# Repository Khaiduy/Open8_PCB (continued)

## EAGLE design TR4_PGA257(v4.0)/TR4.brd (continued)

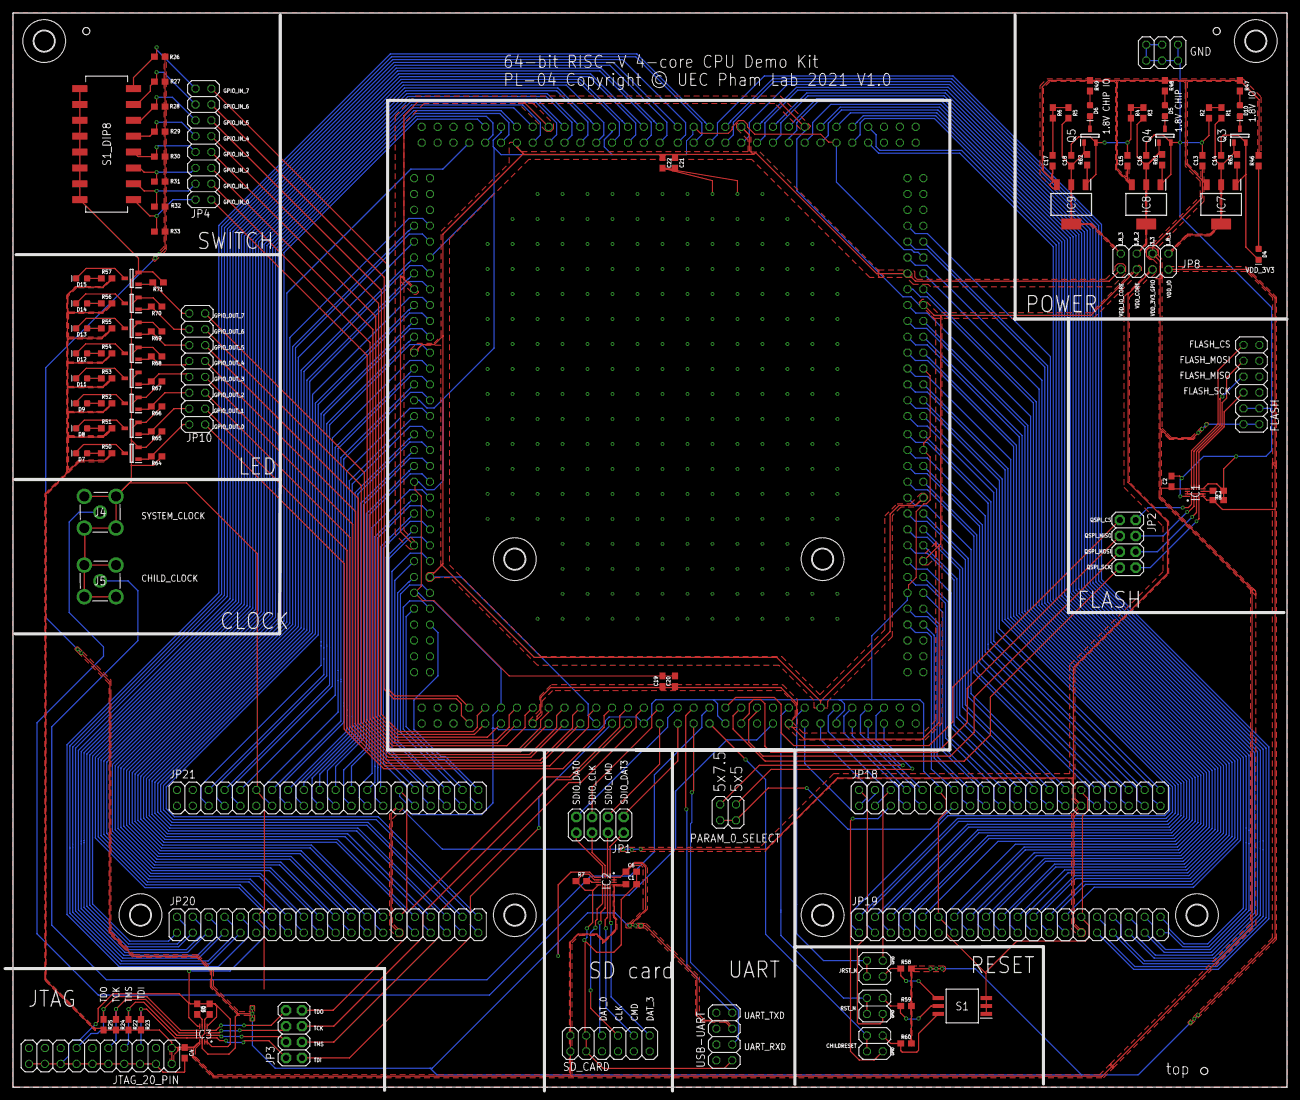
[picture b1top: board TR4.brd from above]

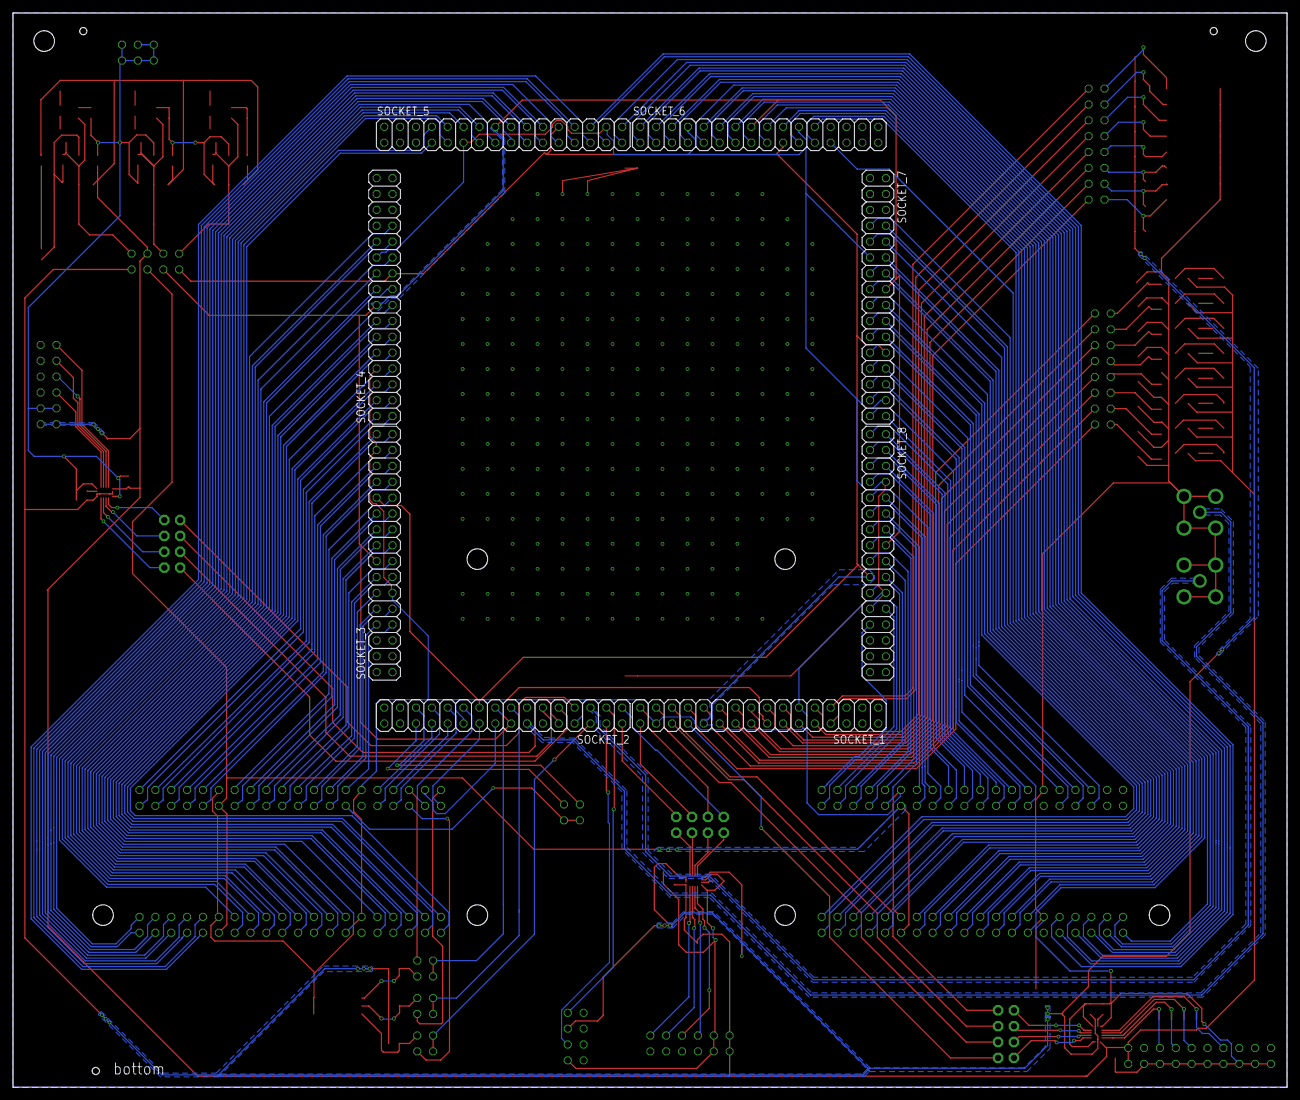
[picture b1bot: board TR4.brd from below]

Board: 2 copper layers, 204.0 x 172.0 mm, 131 parts (8 on the bottom side), 255 nets.

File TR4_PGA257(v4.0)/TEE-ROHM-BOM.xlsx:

Comment | Designator | Footprint | LCSC Part #（optional）
0.1uF | C1, C2, C3, C4, C5, C6, C19, C21 | 603 | C77055
100uF | C14, C16, C18 | 603
10KOHM | R7, R8, R9, R22, R23, R24, R25, R26, R27, R28, R29, R30, R31, R32, R33, R58, R5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 | 603 | C25804
10uF | C13, C15, C17, C20, C22 | 603 | C1691
15KOHM | R1, R3, R5 | 603 | C22809
Switch | S1_DIP8 | 2198LPST | C314503
330OHM | R46, R47, R48, R49, R50, R51, R52, R53, R54, R55, R56, R57 | 603 | C23138
6.8KOHM | R2, R4, R6 | 603 | C23212
BSH103,235 | Q3, Q4, Q5, Q6, Q7, Q8, Q9, Q10, Q11, Q12, Q13 | SOT-23-3 | C88711
DSHP03TSGET | S1 | SW-SMD | C50844
LED0 | D4, D5, D6, D7, D8, D9, D10, D11, D12, D13, D14, D15 | LED-0603 | C2286
LM1117IMPX-ADJ/NOPB | IC7, IC8, IC9 | SOT-223 | C19228
SN74AVC4T774RSVR | IC1, IC2, IC3 | UQFN-16 | C779392

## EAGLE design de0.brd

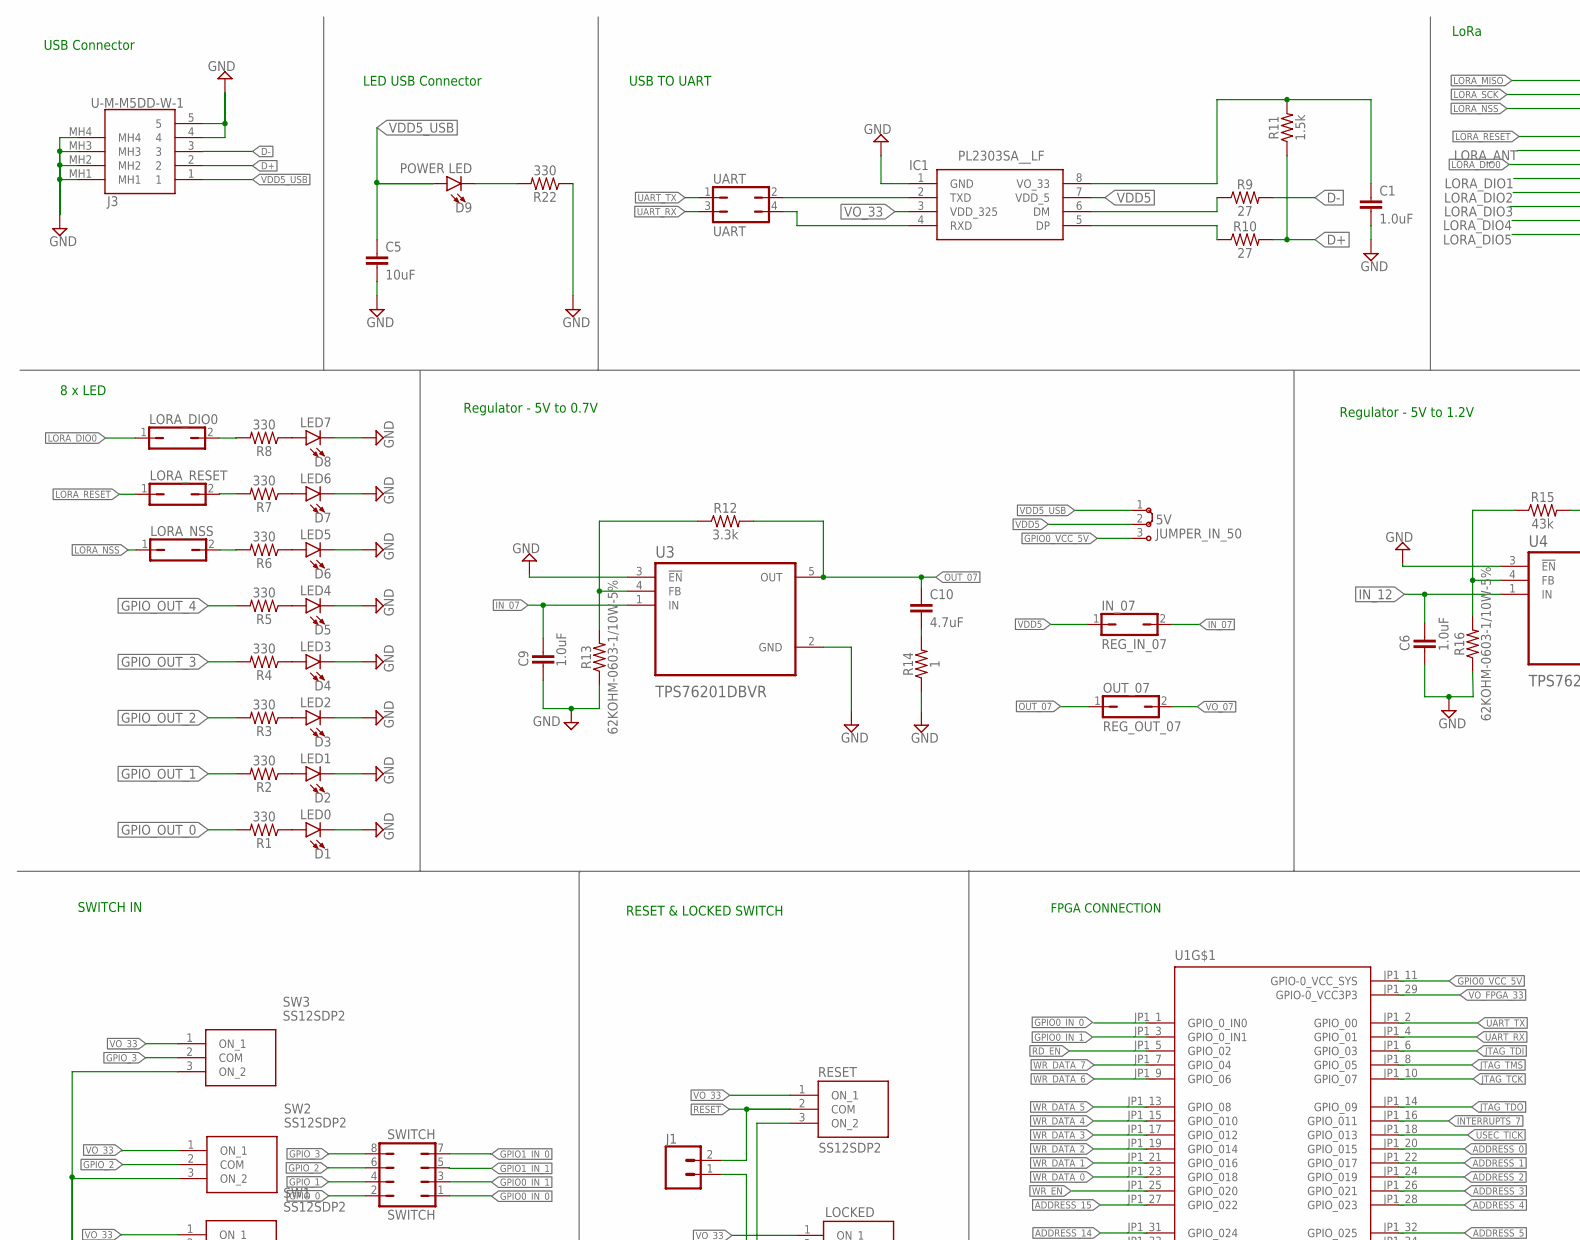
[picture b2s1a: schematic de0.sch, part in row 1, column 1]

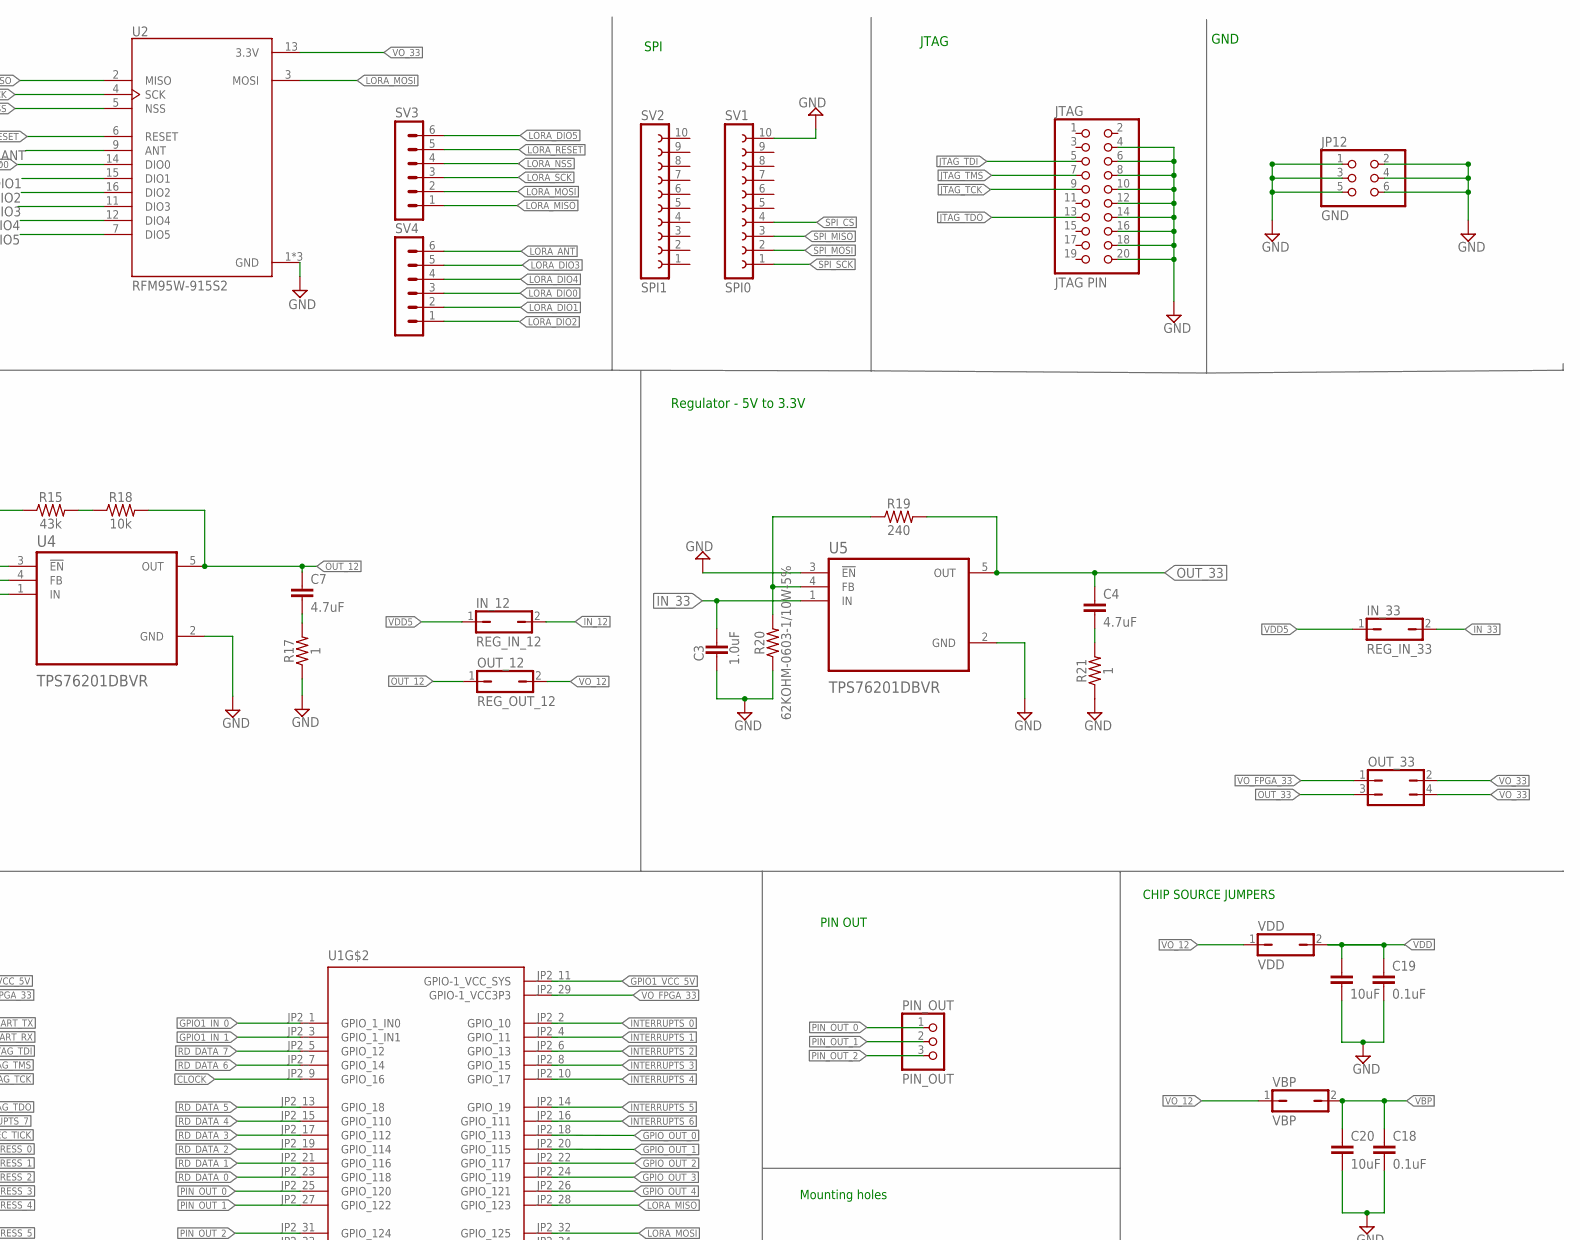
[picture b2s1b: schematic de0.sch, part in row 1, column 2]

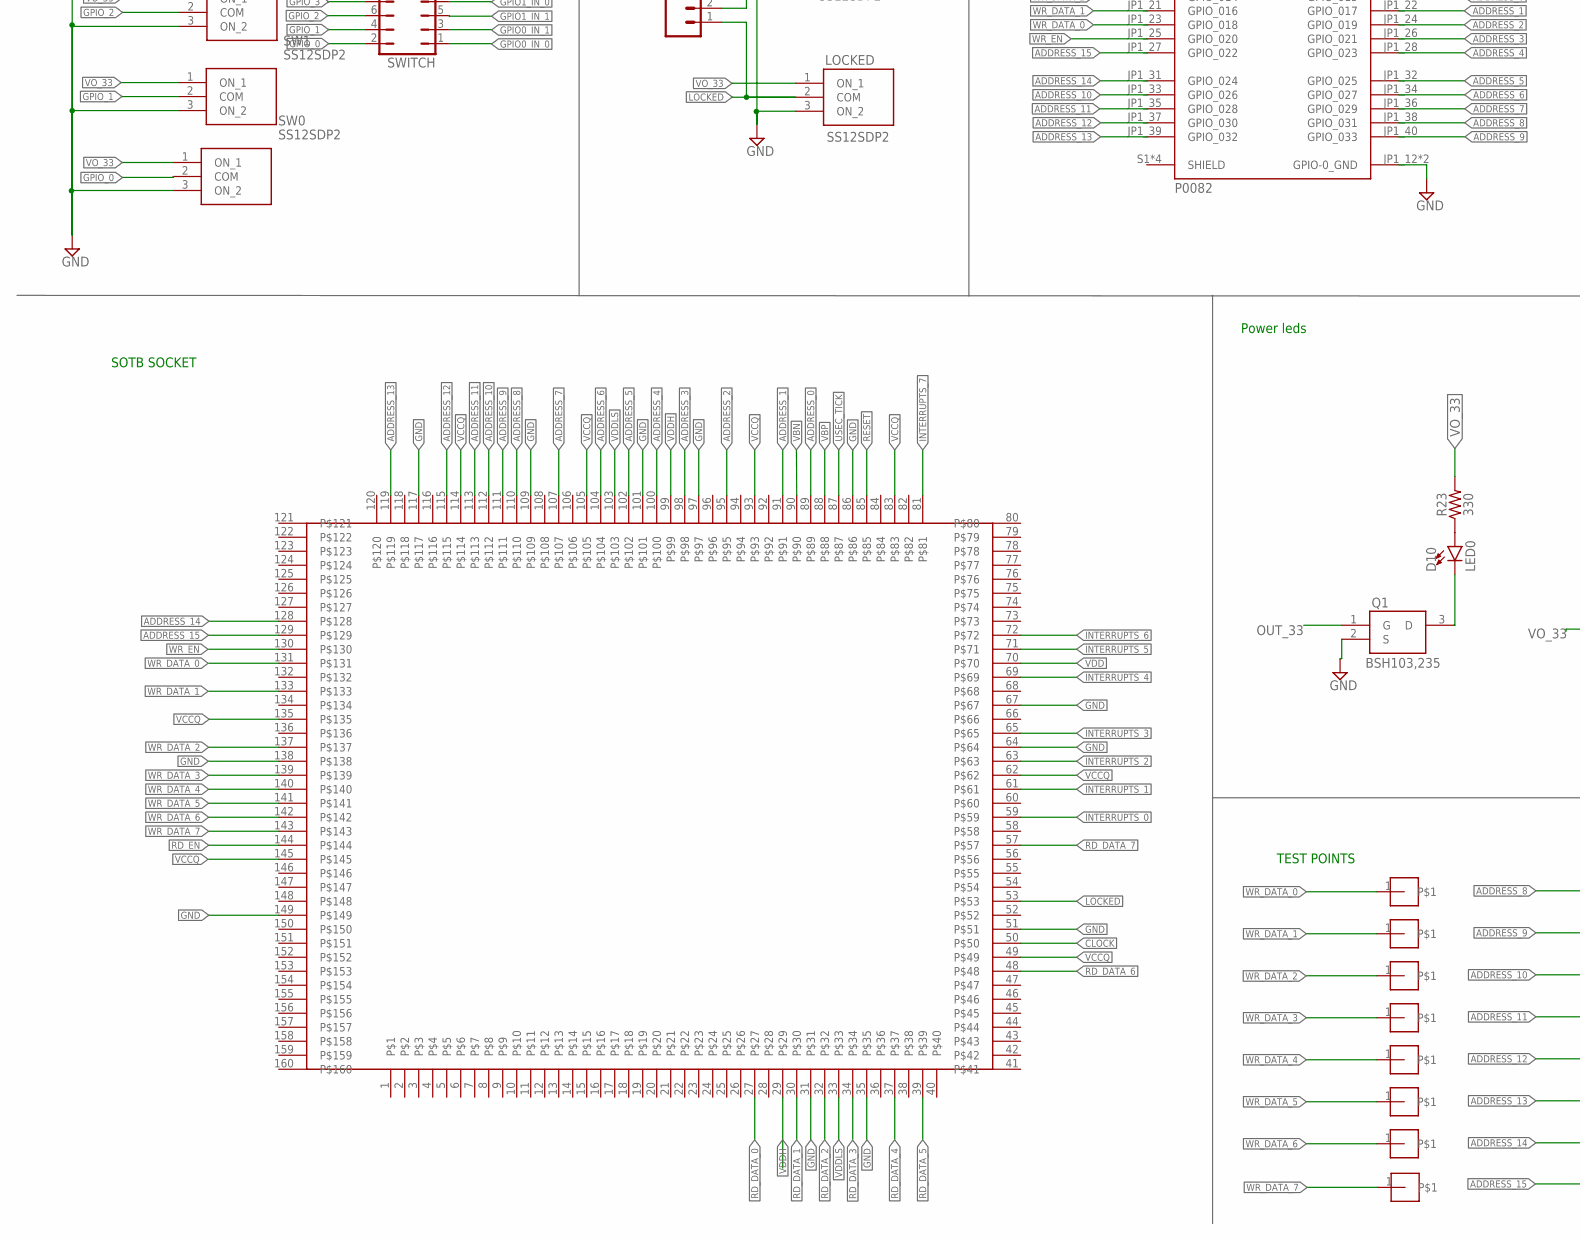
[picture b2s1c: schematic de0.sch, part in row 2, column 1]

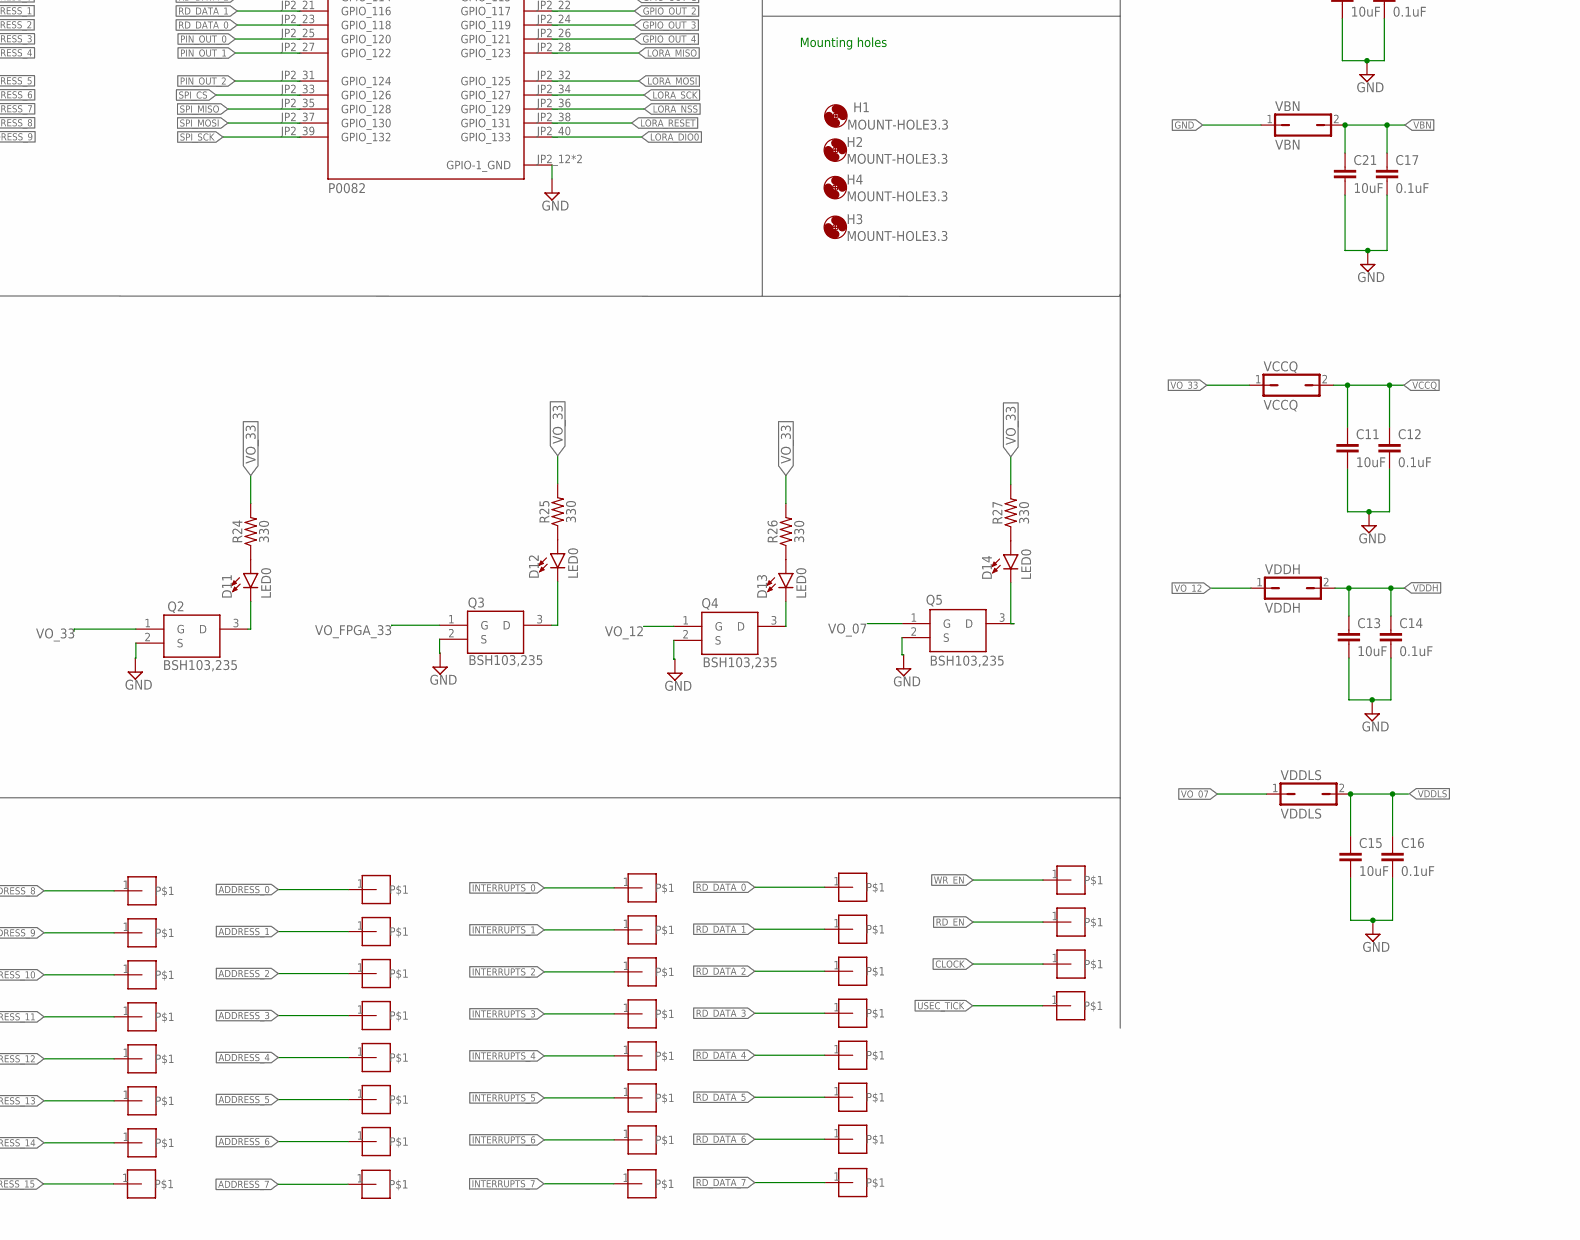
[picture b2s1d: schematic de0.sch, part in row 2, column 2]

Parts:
5V: JUMPER_IN_50; 04C
ADDRESS_0, ADDRESS_1, ADDRESS_2, ADDRESS_3, ADDRESS_4, ADDRESS_5, ADDRESS_6, ADDRESS_7, ADDRESS_8, ADDRESS_9, ADDRESS_10, ADDRESS_11, ADDRESS_12, ADDRESS_13, ADDRESS_14, ADDRESS_15: POINT
C1, C3, C6, C9: 1.0uF; 0603
C4, C7, C10: 4.7uF; 0603
C5, C11, C13, C15, C20, C21, C22: 10uF; 0603
C12, C14, C16, C17, C18, C19: 0.1uF; 0603
CLOCK: POINT
D1, D10, D11, D12, D13, D14: LED0; LED-0603
D2: LED1; LED-0603
D3: LED2; LED-0603
D4: LED3; LED-0603
D5: LED4; LED-0603
D6: LED5; LED-0603
D7: LED6; LED-0603
D8: LED7; LED-0603
D9: POWER LED; LED-0603
H1, H2, H3, H4: MOUNT-HOLE3.3; 3,3
IC1: PL2303SA__LF; SOIC127P600X170-8N
INTERRUPTS_6: INTERRUPTS_6; POINT
IN_07: REG_IN_07; JP1
IN_12: REG_IN_12; JP1
IN_33: REG_IN_33; JP1
J1: CONN_02; 1X02
J3: U-M-M5DD-W-1; UMM5DDW1
JP12: GND; 2X03
JTAG: JTAG PIN; 2X10
LOCKED: SS12SDP2
LORA_DIO0: JP1Q; JP1
LORA_NSS: JP1Q; JP1
LORA_RESET: JP1Q; JP1
OUT_07: REG_OUT_07; JP1
OUT_12: REG_OUT_12; JP1
OUT_33: JP2Q
PIN_OUT: PIN_OUT; 1X03
Q1, Q2, Q3, Q4, Q5: BSH103,235; SOT95P230X110-3N
R1, R2, R3, R4, R5, R6, R7, R8, R22, R23, R24, R25, R26, R27: 330; 0603
R9, R10: 27; 0603
R11: 1.5k; 0603
R12: 3.3k; 0603
R13, R16, R20: 62KOHM-0603-1/10W-5%; 0603
R14, R17, R21: 1; 0603
R15: 43k; 0603
R18: 10k; 0603
R19: 240; 0603
RD_DATA_0, RD_DATA_2, RD_DATA_3, RD_DATA_4, RD_DATA_5, RD_DATA_6, RD_DATA_7: POINT
RD_EN: POINT
RESET: SS12SDP2
SV1: SPI0; FE10
SV2: SPI1; FE10
SV3, SV4: MA06-1
SW0, SW1, SW2, SW3: SS12SDP2
SWITCH: SWITCH; JP4Q
U1: P0082; MODULE_P0082_BOTTOMMOUNT
U2: RFM95W-915S2; XCVR_RFM95W-915S2
U3, U4, U5: TPS76201DBVR; SOT95P280X145-5N
U$1: SOCKET; QFP160_SOCKET
U$4, U$40: POINT
U$10: INTERRUPTS_0; POINT
U$11: INTERRUPTS_1; POINT
U$12: INTERRUPTS_2; POINT
U$13: INTERRUPTS_3; POINT
U$14, U$15: INTERRUPTS_5; POINT
U$17: INTERRUPTS_7; POINT
UART: UART; JP2Q
USEC_TICK: POINT
VBN: VBN; JP1
VBP: VBP; JP1
VCCQ: VCCQ; JP1
VDD: VDD; JP1
VDDH: VDDH; JP1
VDDLS: VDDLS; JP1
WR_DATA_0, WR_DATA_1, WR_DATA_2, WR_DATA_3, WR_DATA_4, WR_DATA_5, WR_DATA_7: POINT
WR_EN: POINT

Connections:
ADDRESS_0: ADDRESS_0.1, U1.JP1_20 (GPIO_015), U$1.89
ADDRESS_1: ADDRESS_1.1, U1.JP1_22 (GPIO_017), U$1.91
ADDRESS_2: ADDRESS_2.1, U1.JP1_24 (GPIO_019), U$1.95
ADDRESS_3: ADDRESS_3.1, U1.JP1_26 (GPIO_021), U$1.98
ADDRESS_4: ADDRESS_4.1, U1.JP1_28 (GPIO_023), U$1.100
ADDRESS_5: ADDRESS_5.1, U1.JP1_32 (GPIO_025), U$1.102
ADDRESS_6: ADDRESS_6.1, U1.JP1_34 (GPIO_027), U$1.104
ADDRESS_7: ADDRESS_7.1, U1.JP1_36 (GPIO_029), U$1.107
ADDRESS_8: ADDRESS_8.1, U1.JP1_38 (GPIO_031), U$1.110
ADDRESS_9: ADDRESS_9.1, U1.JP1_40 (GPIO_033), U$1.111
ADDRESS_10: ADDRESS_10.1, U1.JP1_33 (GPIO_026), U$1.112
ADDRESS_11: ADDRESS_11.1, U1.JP1_35 (GPIO_028), U$1.113
ADDRESS_12: ADDRESS_12.1, U1.JP1_37 (GPIO_030), U$1.115
ADDRESS_13: ADDRESS_13.1, U1.JP1_39 (GPIO_032), U$1.119
ADDRESS_14: ADDRESS_14.1, U1.JP1_31 (GPIO_024), U$1.128
ADDRESS_15: ADDRESS_15.1, U1.JP1_27 (GPIO_022), U$1.129
CLOCK: CLOCK.1, U1.JP2_9 (GPIO_16), U$1.50
D+: J3.2, R10.2, R11.1
D-: J3.3, R9.2
GND: C1.2, C3.2, C5.2, C6.2, C9.2, C11.2, C12.2, C13.2, C14.2, C15.2, C16.2, C17.2, C18.2, C19.2, C20.2, C21.2, C22.2, D1.C, D2.C, D3.C, D4.C, D5.C, D6.C, D7.C, D8.C, IC1.1 (GND), J3.4, J3.5, J3.MH1, J3.MH2, J3.MH3, J3.MH4, JP12.1, JP12.2, JP12.3, JP12.4, JP12.5, JP12.6, JTAG.4, JTAG.6, JTAG.8, JTAG.10, JTAG.12, JTAG.14, JTAG.16, JTAG.18, JTAG.20, LOCKED.3 (ON_2), Q1.2 (S), Q2.2 (S), Q3.2 (S), Q4.2 (S), Q5.2 (S), R13.1, R14.1, R16.1, R17.1, R20.1, R21.1, R22.1, RESET.3 (ON_2), SV1.10, SW0.3 (ON_2), SW1.3 (ON_2), SW2.3 (ON_2), SW3.3 (ON_2), U1.JP1_12 (GPIO-0_GND), U1.JP1_30 (GPIO-0_GND), U1.JP2_12 (GPIO-1_GND), U1.JP2_30 (GPIO-1_GND), U2.1 (GND), U2.8 (GND), U2.10 (GND), U3.2 (GND), U3.3 (!EN), U4.2 (GND), U4.3 (!EN), U5.2 (GND), U5.3 (!EN), U$1.31, U$1.35, U$1.51, U$1.64, U$1.67, U$1.86, U$1.97, U$1.101, U$1.109, U$1.117, U$1.138, U$1.149, VBN.1
GPIO0_IN_0: SWITCH.1, U1.JP1_1 (GPIO_0_IN0)
GPIO0_IN_1: SWITCH.3, U1.JP1_3 (GPIO_0_IN1)
GPIO0_VCC_5V: 5V.3, U1.JP1_11 (GPIO-0_VCC_SYS)
GPIO1_IN_0: SWITCH.7, U1.JP2_1 (GPIO_1_IN0)
GPIO1_IN_1: SWITCH.5, U1.JP2_3 (GPIO_1_IN1)
GPIO1_VCC_5V: U1.JP2_11 (GPIO-1_VCC_SYS)
GPIO_0: SW0.2 (COM), SWITCH.2
GPIO_1: SW1.2 (COM), SWITCH.4
GPIO_2: SW2.2 (COM), SWITCH.6
GPIO_3: SW3.2 (COM), SWITCH.8
GPIO_OUT_0: R1.2, U1.JP2_18 (GPIO_113)
GPIO_OUT_1: R2.2, U1.JP2_20 (GPIO_115)
GPIO_OUT_2: R3.2, U1.JP2_22 (GPIO_117)
GPIO_OUT_3: R4.2, U1.JP2_24 (GPIO_119)
GPIO_OUT_4: R5.2, U1.JP2_26 (GPIO_121)
INTERRUPTS_0: U1.JP2_2 (GPIO_10), U$1.59, U$10.1
INTERRUPTS_1: U1.JP2_4 (GPIO_11), U$1.61, U$11.1
INTERRUPTS_2: U1.JP2_6 (GPIO_13), U$1.63, U$12.1
INTERRUPTS_3: U1.JP2_8 (GPIO_15), U$1.65, U$13.1
INTERRUPTS_4: U1.JP2_10 (GPIO_17), U$1.69, U$14.1
INTERRUPTS_5: U1.JP2_14 (GPIO_19), U$1.71, U$15.1
INTERRUPTS_6: INTERRUPTS_6.1, U1.JP2_16 (GPIO_111), U$1.72
INTERRUPTS_7: U1.JP1_16 (GPIO_011), U$1.81, U$17.1
IN_07: C9.1, IN_07.2, U3.1 (IN)
IN_12: C6.1, IN_12.2, U4.1 (IN)
IN_33: C3.1, IN_33.2, U5.1 (IN)
JTAG_TCK: JTAG.9, U1.JP1_10 (GPIO_07)
JTAG_TDI: JTAG.5, U1.JP1_6 (GPIO_03)
JTAG_TDO: JTAG.13, U1.JP1_14 (GPIO_09)
JTAG_TMS: JTAG.7, U1.JP1_8 (GPIO_05)
LOCKED: J1.1, LOCKED.2 (COM), U$1.53
LORA_ANT: SV4.6, U2.9 (ANT)
LORA_DIO0: LORA_DIO0.1, SV4.3, U1.JP2_40 (GPIO_133), U2.14 (DIO0)
LORA_DIO1: SV4.2, U2.15 (DIO1)
LORA_DIO2: SV4.1, U2.16 (DIO2)
LORA_DIO3: SV4.5, U2.11 (DIO3)
LORA_DIO4: SV4.4, U2.12 (DIO4)
LORA_DIO5: SV3.6, U2.7 (DIO5)
LORA_MISO: SV3.1, U1.JP2_28 (GPIO_123), U2.2 (MISO)
LORA_MOSI: SV3.2, U1.JP2_32 (GPIO_125), U2.3 (MOSI)
LORA_NSS: LORA_NSS.1, SV3.4, U1.JP2_36 (GPIO_129), U2.5 (NSS)
LORA_RESET: LORA_RESET.1, SV3.5, U1.JP2_38 (GPIO_131), U2.6 (RESET)
LORA_SCK: SV3.3, U1.JP2_34 (GPIO_127), U2.4 (SCK)
unnamed: D1.A, R1.1
unnamed: D8.A, R8.1
unnamed: D7.A, R7.1
unnamed: D6.A, R6.1
unnamed: D5.A, R5.1
unnamed: D4.A, R4.1
unnamed: D2.A, R2.1
unnamed: D3.A, R3.1
unnamed: D10.A, R23.1
unnamed: D10.C, Q1.3 (D)
unnamed: D12.A, R25.1
unnamed: D12.C, Q3.3 (D)
unnamed: D11.A, R24.1
unnamed: D11.C, Q2.3 (D)
unnamed: D13.A, R26.1
unnamed: D13.C, Q4.3 (D)
unnamed: IC1.6 (DM), R9.1
unnamed: D14.A, R27.1
unnamed: D14.C, Q5.3 (D)
unnamed: IC1.5 (DP), R10.1
unnamed: IC1.2 (TXD), UART.2
unnamed: IC1.4 (RXD), UART.4
unnamed: LORA_DIO0.2, R8.2
unnamed: LORA_RESET.2, R7.2
unnamed: LORA_NSS.2, R6.2
unnamed: R12.1, R13.2, U3.4 (FB)
unnamed: R15.1, R16.2, U4.4 (FB)
unnamed: C10.2, R14.2
unnamed: C7.2, R17.2
unnamed: R15.2, R18.1
unnamed: R19.1, R20.2, U5.4 (FB)
unnamed: C4.2, R21.2
unnamed: D9.C, R22.2
OUT_07: C10.1, OUT_07.1, R12.2, U3.5 (OUT)
OUT_12: C7.1, OUT_12.1, R18.2, U4.5 (OUT)
OUT_33: C4.1, OUT_33.3, Q1.1 (G), R19.2, U5.5 (OUT)
PIN_OUT_0: PIN_OUT.1, U1.JP2_25 (GPIO_120)
PIN_OUT_1: PIN_OUT.2, U1.JP2_27 (GPIO_122)
PIN_OUT_2: PIN_OUT.3, U1.JP2_31 (GPIO_124)
RD_DATA_0: RD_DATA_0.1, U1.JP2_23 (GPIO_118), U$1.27
RD_DATA_1: U1.JP2_21 (GPIO_116), U$1.30, U$4.1
RD_DATA_2: RD_DATA_2.1, U1.JP2_19 (GPIO_114), U$1.32
RD_DATA_3: RD_DATA_3.1, U1.JP2_17 (GPIO_112), U$1.34
RD_DATA_4: RD_DATA_4.1, U1.JP2_15 (GPIO_110), U$1.37
RD_DATA_5: RD_DATA_5.1, U1.JP2_13 (GPIO_18), U$1.39
RD_DATA_6: RD_DATA_6.1, U1.JP2_7 (GPIO_14), U$1.48
RD_DATA_7: RD_DATA_7.1, U1.JP2_5 (GPIO_12), U$1.57
RD_EN: RD_EN.1, U1.JP1_5 (GPIO_02), U$1.144
RESET: J1.2, RESET.2 (COM), U$1.85
SPI_CS: SV1.4, U1.JP2_33 (GPIO_126)
SPI_MISO: SV1.3, U1.JP2_35 (GPIO_128)
SPI_MOSI: SV1.2, U1.JP2_37 (GPIO_130)
SPI_SCK: SV1.1, U1.JP2_39 (GPIO_132)
UART_RX: U1.JP1_4 (GPIO_01), UART.3
UART_TX: U1.JP1_2 (GPIO_00), UART.1
USEC_TICK: U1.JP1_18 (GPIO_013), U$1.87, USEC_TICK.1
VBN: C17.1, C21.1, U$1.90, VBN.2
VBP: C18.1, C20.1, U$1.88, VBP.2
VCCQ: C11.1, C12.1, U$1.49, U$1.62, U$1.83, U$1.93, U$1.105, U$1.114, U$1.135, U$1.145, VCCQ.2
VDD: C19.1, C22.1, U$1.70, VDD.2
VDD5: 5V.2, IC1.7 (VDD_5), IN_07.1, IN_12.1, IN_33.1
VDD5_USB: 5V.1, C5.1, D9.A, J3.1
VDDH: C13.1, C14.1, U$1.29, U$1.99, VDDH.2
VDDLS: C15.1, C16.1, U$1.33, U$1.103, VDDLS.2
VO_07: OUT_07.2, Q5.1 (G), VDDLS.1
VO_12: OUT_12.2, Q4.1 (G), VBP.1, VDD.1, VDDH.1
VO_33: C1.1, IC1.3 (VDD_325), IC1.8 (VO_33), LOCKED.1 (ON_1), OUT_33.2, OUT_33.4, Q2.1 (G), R11.2, R23.2, R24.2, R25.2, R26.2, R27.2, RESET.1 (ON_1), SW0.1 (ON_1), SW1.1 (ON_1), SW2.1 (ON_1), SW3.1 (ON_1), U2.13 (3.3V), VCCQ.1
VO_FPGA_33: OUT_33.1, Q3.1 (G), U1.JP1_29 (GPIO-0_VCC3P3), U1.JP2_29 (GPIO-1_VCC3P3)
WR_DATA_0: U1.JP1_23 (GPIO_018), U$1.131, WR_DATA_0.1
WR_DATA_1: U1.JP1_21 (GPIO_016), U$1.133, WR_DATA_1.1
WR_DATA_2: U1.JP1_19 (GPIO_014), U$1.137, WR_DATA_2.1
WR_DATA_3: U1.JP1_17 (GPIO_012), U$1.139, WR_DATA_3.1
WR_DATA_4: U1.JP1_15 (GPIO_010), U$1.140, WR_DATA_4.1
WR_DATA_5: U1.JP1_13 (GPIO_08), U$1.141, WR_DATA_5.1
WR_DATA_6: U1.JP1_9 (GPIO_06), U$1.142, U$40.1
WR_DATA_7: U1.JP1_7 (GPIO_04), U$1.143, WR_DATA_7.1
WR_EN: U1.JP1_25 (GPIO_020), U$1.130, WR_EN.1

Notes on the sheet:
LED USB Connector
USB TO UART
8 x LED
Regulator - 5V to 0.7V
Regulator - 5V to 1.2V
Regulator - 5V to 3.3V
LoRa
SPI
JTAG
GND
SWITCH IN
RESET & LOCKED SWITCH
FPGA CONNECTION
PIN OUT
CHIP SOURCE JUMPERS
SOTB SOCKET
TEST POINTS
Mounting holes
Power leds
USB Connector

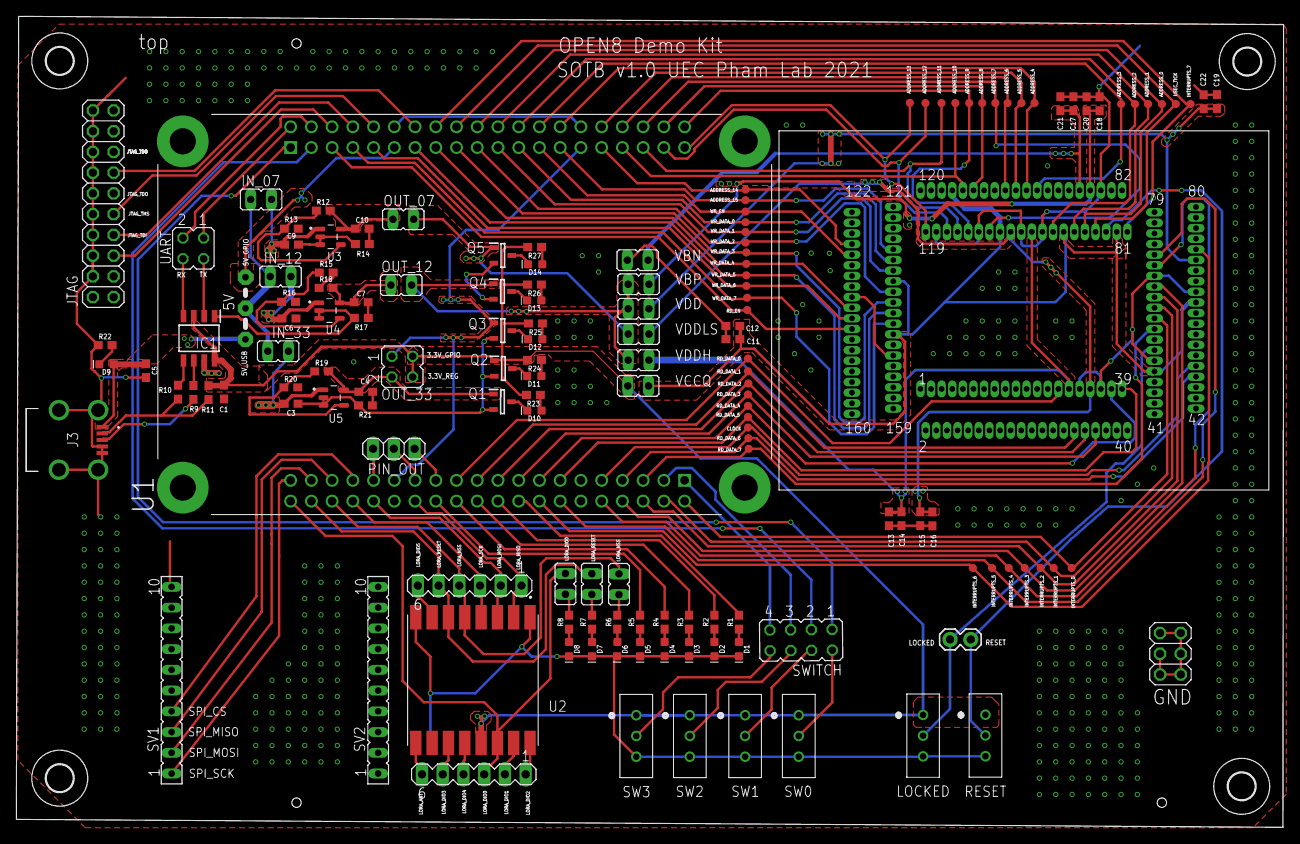
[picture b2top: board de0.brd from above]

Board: 2 copper layers, 155.2 x 99.3 mm, 154 parts (0 on the bottom side), 139 nets.

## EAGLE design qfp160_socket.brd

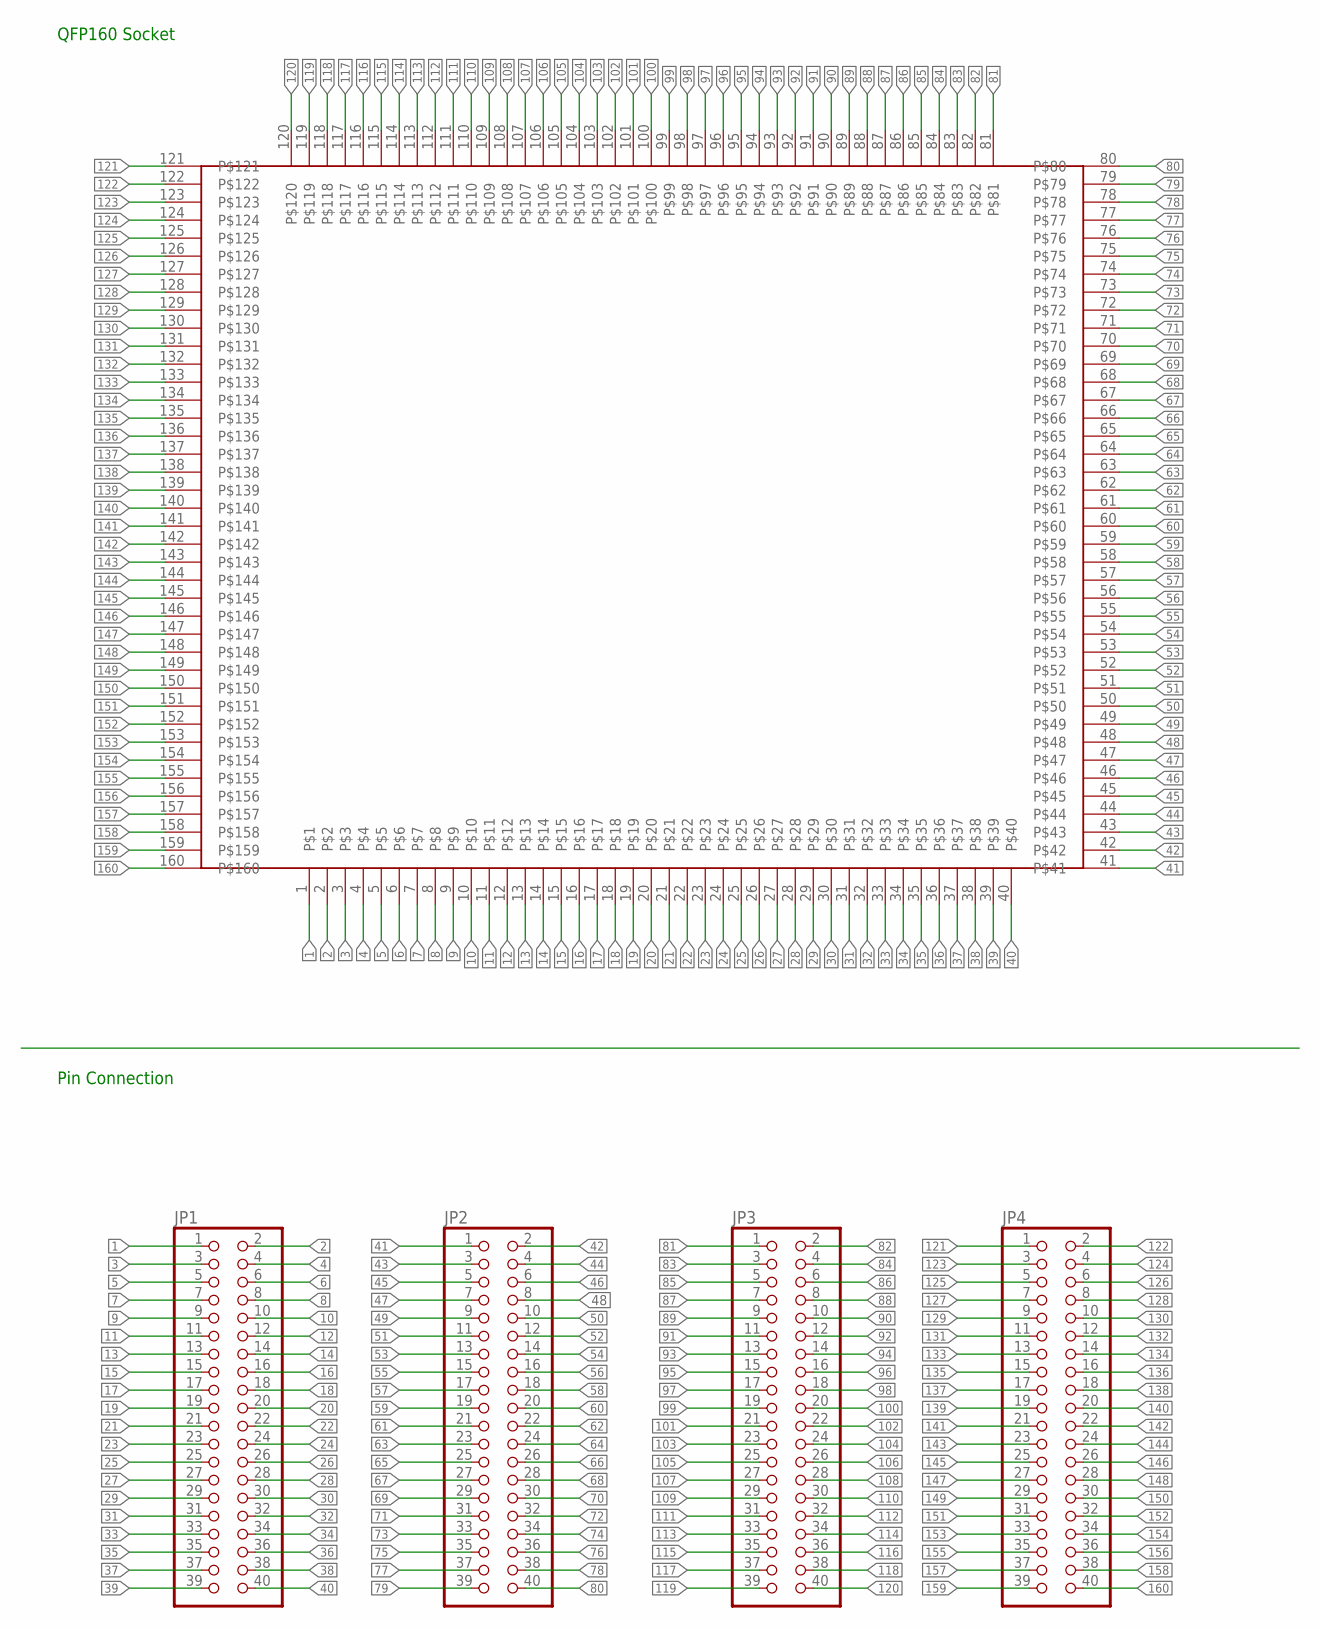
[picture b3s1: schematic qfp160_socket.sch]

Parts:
JP1, JP2, JP3, JP4: PINHD-2X20; 2X20
U$1: QFP160_SOCKET

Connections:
1: JP1.1, U$1.1
2: JP1.2, U$1.2
3: JP1.3, U$1.3
4: JP1.4, U$1.4
5: JP1.5, U$1.5
6: JP1.6, U$1.6
7: JP1.7, U$1.7
8: JP1.8, U$1.8
9: JP1.9, U$1.9
10: JP1.10, U$1.10
11: JP1.11, U$1.11
12: JP1.12, U$1.12
13: JP1.13, U$1.13
14: JP1.14, U$1.14
15: JP1.15, U$1.15
16: JP1.16, U$1.16
17: JP1.17, U$1.17
18: JP1.18, U$1.18
19: JP1.19, U$1.19
20: JP1.20, U$1.20
21: JP1.21, U$1.21
22: JP1.22, U$1.22
23: JP1.23, U$1.23
24: JP1.24, U$1.24
25: JP1.25, U$1.25
26: JP1.26, U$1.26
27: JP1.27, U$1.27
28: JP1.28, U$1.28
29: JP1.29, U$1.29
30: JP1.30, U$1.30
31: JP1.31, U$1.31
32: JP1.32, U$1.32
33: JP1.33, U$1.33
34: JP1.34, U$1.34
35: JP1.35, U$1.35
36: JP1.36, U$1.36
37: JP1.37, U$1.37
38: JP1.38, U$1.38
39: JP1.39, U$1.39
40: JP1.40, U$1.40
41: JP2.1, U$1.41
42: JP2.2, U$1.42
43: JP2.3, U$1.43
44: JP2.4, U$1.44
45: JP2.5, U$1.45
46: JP2.6, U$1.46
47: JP2.7, U$1.47
48: JP2.8, U$1.48
49: JP2.9, U$1.49
50: JP2.10, U$1.50
51: JP2.11, U$1.51
52: JP2.12, U$1.52
53: JP2.13, U$1.53
54: JP2.14, U$1.54
55: JP2.15, U$1.55
56: JP2.16, U$1.56
57: JP2.17, U$1.57
58: JP2.18, U$1.58
59: JP2.19, U$1.59
60: JP2.20, U$1.60
61: JP2.21, U$1.61
62: JP2.22, U$1.62
63: JP2.23, U$1.63
64: JP2.24, U$1.64
65: JP2.25, U$1.65
66: JP2.26, U$1.66
67: JP2.27, U$1.67
68: JP2.28, U$1.68
69: JP2.29, U$1.69
70: JP2.30, U$1.70
71: JP2.31, U$1.71
72: JP2.32, U$1.72
73: JP2.33, U$1.73
74: JP2.34, U$1.74
75: JP2.35, U$1.75
76: JP2.36, U$1.76
77: JP2.37, U$1.77
78: JP2.38, U$1.78
79: JP2.39, U$1.79
80: JP2.40, U$1.80
81: JP3.1, U$1.81
82: JP3.2, U$1.82
83: JP3.3, U$1.83
84: JP3.4, U$1.84
85: JP3.5, U$1.85
86: JP3.6, U$1.86
87: JP3.7, U$1.87
88: JP3.8, U$1.88
89: JP3.9, U$1.89
90: JP3.10, U$1.90
91: JP3.11, U$1.91
92: JP3.12, U$1.92
93: JP3.13, U$1.93
94: JP3.14, U$1.94
95: JP3.15, U$1.95
96: JP3.16, U$1.96
97: JP3.17, U$1.97
98: JP3.18, U$1.98
99: JP3.19, U$1.99
100: JP3.20, U$1.100
101: JP3.21, U$1.101
102: JP3.22, U$1.102
103: JP3.23, U$1.103
104: JP3.24, U$1.104
105: JP3.25, U$1.105
106: JP3.26, U$1.106
107: JP3.27, U$1.107
108: JP3.28, U$1.108
109: JP3.29, U$1.109
110: JP3.30, U$1.110
111: JP3.31, U$1.111
112: JP3.32, U$1.112
113: JP3.33, U$1.113
114: JP3.34, U$1.114
115: JP3.35, U$1.115
116: JP3.36, U$1.116
117: JP3.37, U$1.117
118: JP3.38, U$1.118
119: JP3.39, U$1.119
120: JP3.40, U$1.120
121: JP4.1, U$1.121
122: JP4.2, U$1.122
123: JP4.3, U$1.123
124: JP4.4, U$1.124
125: JP4.5, U$1.125
126: JP4.6, U$1.126
127: JP4.7, U$1.127
128: JP4.8, U$1.128
129: JP4.9, U$1.129
130: JP4.10, U$1.130
131: JP4.11, U$1.131
132: JP4.12, U$1.132
133: JP4.13, U$1.133
134: JP4.14, U$1.134
135: JP4.15, U$1.135
136: JP4.16, U$1.136
137: JP4.17, U$1.137
138: JP4.18, U$1.138
139: JP4.19, U$1.139
140: JP4.20, U$1.140
141: JP4.21, U$1.141
142: JP4.22, U$1.142
143: JP4.23, U$1.143
144: JP4.24, U$1.144
145: JP4.25, U$1.145
146: JP4.26, U$1.146
147: JP4.27, U$1.147
148: JP4.28, U$1.148
149: JP4.29, U$1.149
150: JP4.30, U$1.150
151: JP4.31, U$1.151
152: JP4.32, U$1.152
153: JP4.33, U$1.153
154: JP4.34, U$1.154
155: JP4.35, U$1.155
156: JP4.36, U$1.156
157: JP4.37, U$1.157
158: JP4.38, U$1.158
159: JP4.39, U$1.159
160: JP4.40, U$1.160

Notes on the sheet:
QFP160 Socket
Pin Connection

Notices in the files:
TR4_PGA257(v4.0)/TR4.brd:
PL-04 Copyright © UEC Pham Lab 2021 V1.0
parts and their libraries:
SparkFun-Capacitors: Licensing: Creative Commons ShareAlike 4.0 International - https://creativecommons.org/licenses/by-sa/4.0
